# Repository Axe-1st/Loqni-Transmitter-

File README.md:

# Loqni-Transmitter-
> An Attachment for your phone or laptop to communicate outdoors! You could use this for camping. Powered by an Xiao Esp32c3 and Ra-02_module!
This Project requires 2 modules. It works by opening a webportal which you use to talk/messsage to the eps32c3 then it will direct the message in a spicific channel by ussing the ra -02 module

<h2>OVERVIEW</h2>

-no ra-02 module stl online

> It has:
+ 3.7 bat
+ momentary button
+ xiao esp 32c3
+ Ra-02 module
+ sma pigtail
+ Antena 433mhz
+ Power Switch
+ Pcb
+ Case

<h3>PCB</h3>

-1st version

-2nd version

<h3>schematic</h3>

<h3>Case</h3>
> 4 part and multiplied by 2! 

<h2>Bill of Materials</h2>

-some in php 

-Budget 50 + 15 dollars top up

-CONVERSION RATE: 1 United States Dollar equals 57.57 Philippine peso

[View the full BOM SHEET here](./Main/BOM/Untitled%20spreadsheet%20-%20Sheet1.csv)

<h2>Shopee info</h2>

-GRANT:₱3741.79/$65

-MERCHANDISE TOTAL: ₱1,764

-SHIPPING TOTAL:₱344

-VOUCHER DISCOUNT: -₱29

-ALL TOTAL:₱2,079/$36.12

-REMAINING:₱1663/$28.89

*Shipping fee changes/fluxuates but the shipping above sometimes its free*

<h2>JLC PCB</h2>
-5 pcb
-$3.50 or 201.09 php
-remaining:₱1462 /$25.40

-Printing legion (around 10 or more dollars)
-remaining ₱886.34/$15.40 (will give the remaining money back)

-Not included:
-SK6812MINI-E (i still have)

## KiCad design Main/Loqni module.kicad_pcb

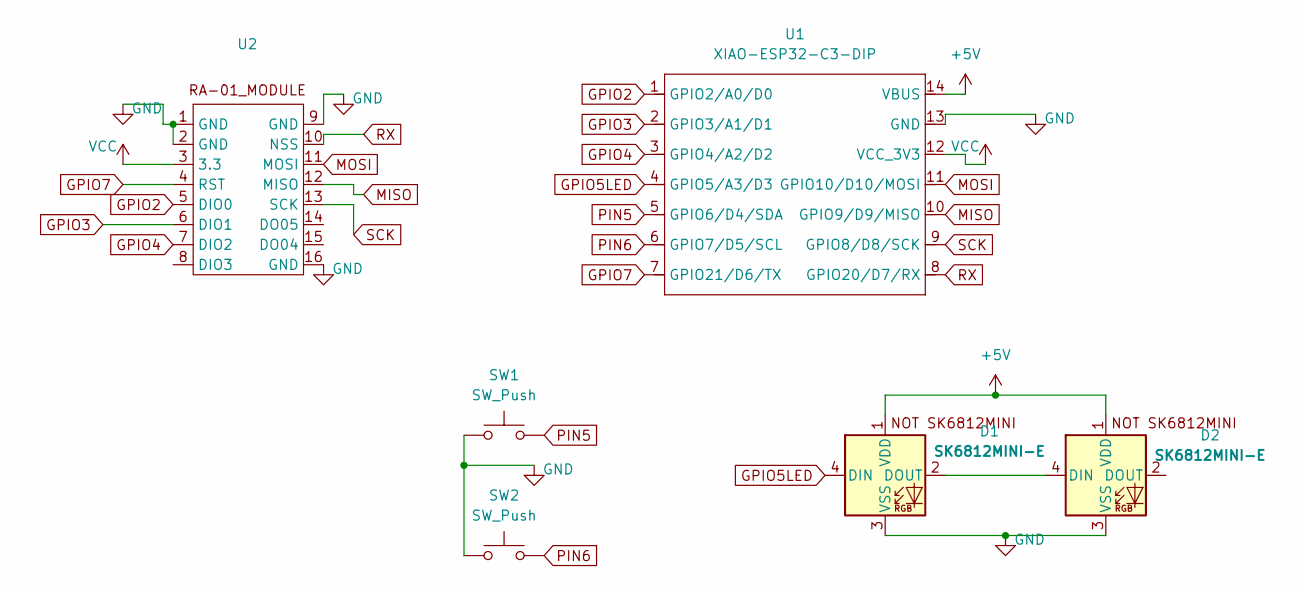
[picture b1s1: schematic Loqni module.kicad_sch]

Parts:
D1, D2: SK6812MINI-E; SK6812MINI-E_fixed
SW1, SW2: SW_Push; SW_PUSH_6mm
U1: XIAO-ESP32-C3-DIP; XIAO-ESP32C3-DIP
U2: DIP-16_1100_ELLfixed

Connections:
+5V: D1.1 (VDD), D2.1 (VDD), U1.14 (VBUS)
GND: D1.3 (VSS), D2.3 (VSS), SW1.1, SW2.1, U1.13 (GND), U2.1 (GND), U2.2 (GND), U2.9 (GND), U2.16 (GND)
GPIO2: U1.1 (GPIO2/A0/D0), U2.5 (DIO0)
GPIO3: U1.2 (GPIO3/A1/D1), U2.6 (DIO1)
GPIO4: U1.3 (GPIO4/A2/D2), U2.7 (DIO2)
GPIO5LED: D1.4 (DIN), U1.4 (GPIO5/A3/D3)
GPIO7: U1.7 (GPIO21/D6/TX), U2.4 (RST)
MISO: U1.10 (GPIO9/D9/MISO), U2.12 (MISO)
MOSI: U1.11 (GPIO10/D10/MOSI), U2.11 (MOSI)
unnamed: D1.2 (DOUT), D2.4 (DIN)
PIN5: SW1.2, U1.5 (GPIO6/D4/SDA)
PIN6: SW2.2, U1.6 (GPIO7/D5/SCL)
RX: U1.8 (GPIO20/D7/RX), U2.10 (NSS)
SCK: U1.9 (GPIO8/D8/SCK), U2.13 (SCK)
VCC: U1.12 (VCC_3V3), U2.3 (3.3)

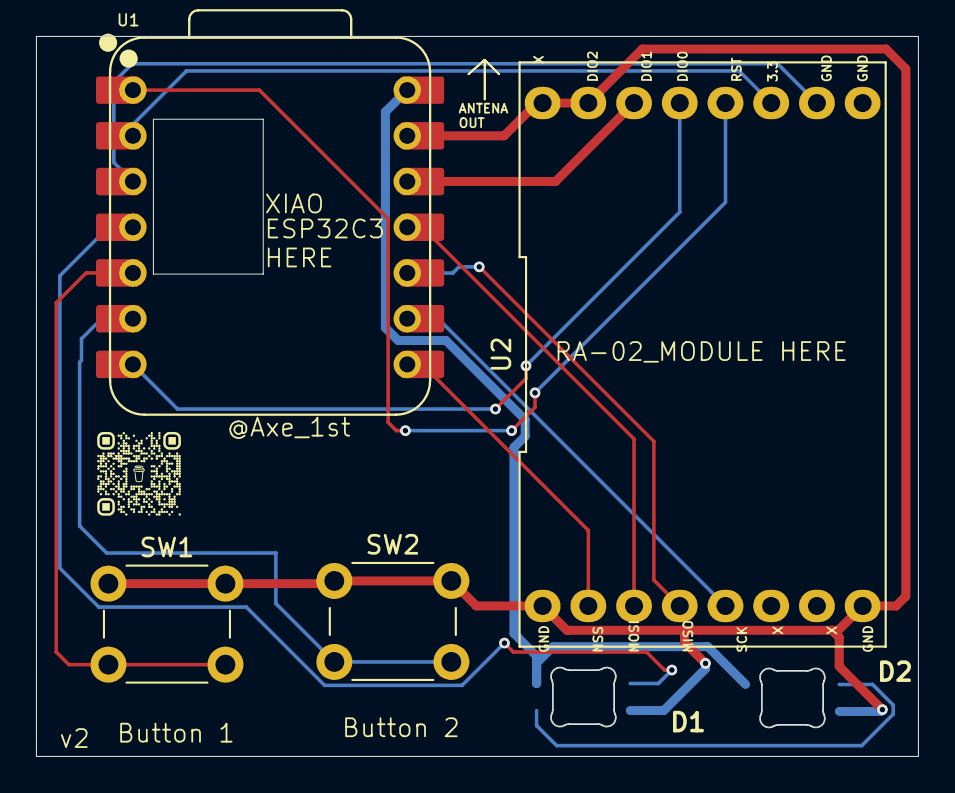
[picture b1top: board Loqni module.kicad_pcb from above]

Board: 2 copper layers, 49.0 x 40.0 mm, 6 parts (0 on the bottom side), 15 nets.

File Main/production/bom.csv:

Designator,Footprint,Quantity,Value,LCSC Part #
"D1, D2",SK6812MINI-E_fixed,2,SK6812MINI-E,
"SW1, SW2",SW_PUSH_6mm,2,SW_Push,
U1,XIAO-ESP32C3-DIP,1,XIAO-ESP32-C3-DIP,
U2,DIP-16_600_ELL,1,~,

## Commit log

2026-02-25 First commit i guess
2026-02-26 Readme edit
2026-02-27 Cad and Firmware
2026-02-28 added img!
2026-02-28 Add image for 1st version PCB in README
2026-02-28 imgs
2026-02-28 Enhance README with project details and images
    Updated project description and added images for PCB versions and case.
2026-02-28 more
2026-02-28 more Img
2026-02-28 Fix formatting and update descriptions in README
    Updated text formatting and corrected some descriptions in the README.
2026-02-28 Update README with project components and features
    Added details about components and features of the project.
2026-03-05 New BOM
2026-03-05 Clean up Shopee product details in README
    Removed specific product details and prices from the Shopee section.
